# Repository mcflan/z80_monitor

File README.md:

# Z80 Monitor

</img>

A device that allows a host PC to read and write memory on the bus of a Z80
computer (or potentially other CPUs) as well as a few other functions. It makes
use of the Z80's BUSRQ / BUSAK feature to gain access to the bus while the CPU
is running. The circuit is based on an Atmel atmega1281. The host interface is
a bidirectional TTL-level serial (UART) connection that uses a simple hex-based
protocol to control the monitor and provide handshaking. The host interface is
electrically isolated to allow the target device to be power-cycled properly
without being back-powered by the serial signals. This also avoids any risk of
SCR latch-up.

## Host Connector

This is 6-way single-row header to fit a standard FTDI FT232 serial cable (TTL type.) It will work with the 5V and 3V3 versions.

 | Number | Function      |
 |:------:|:------------- |
 |  6     | Not Used      |
 |  5     | Serial Out    |
 |  4     | Serial In     |
 |  3     | Power In      |
 |  2     | Not Used      |
 |  1     | Ground        |

## Bus Connector

See the [pinout file](bus_pinout.md)

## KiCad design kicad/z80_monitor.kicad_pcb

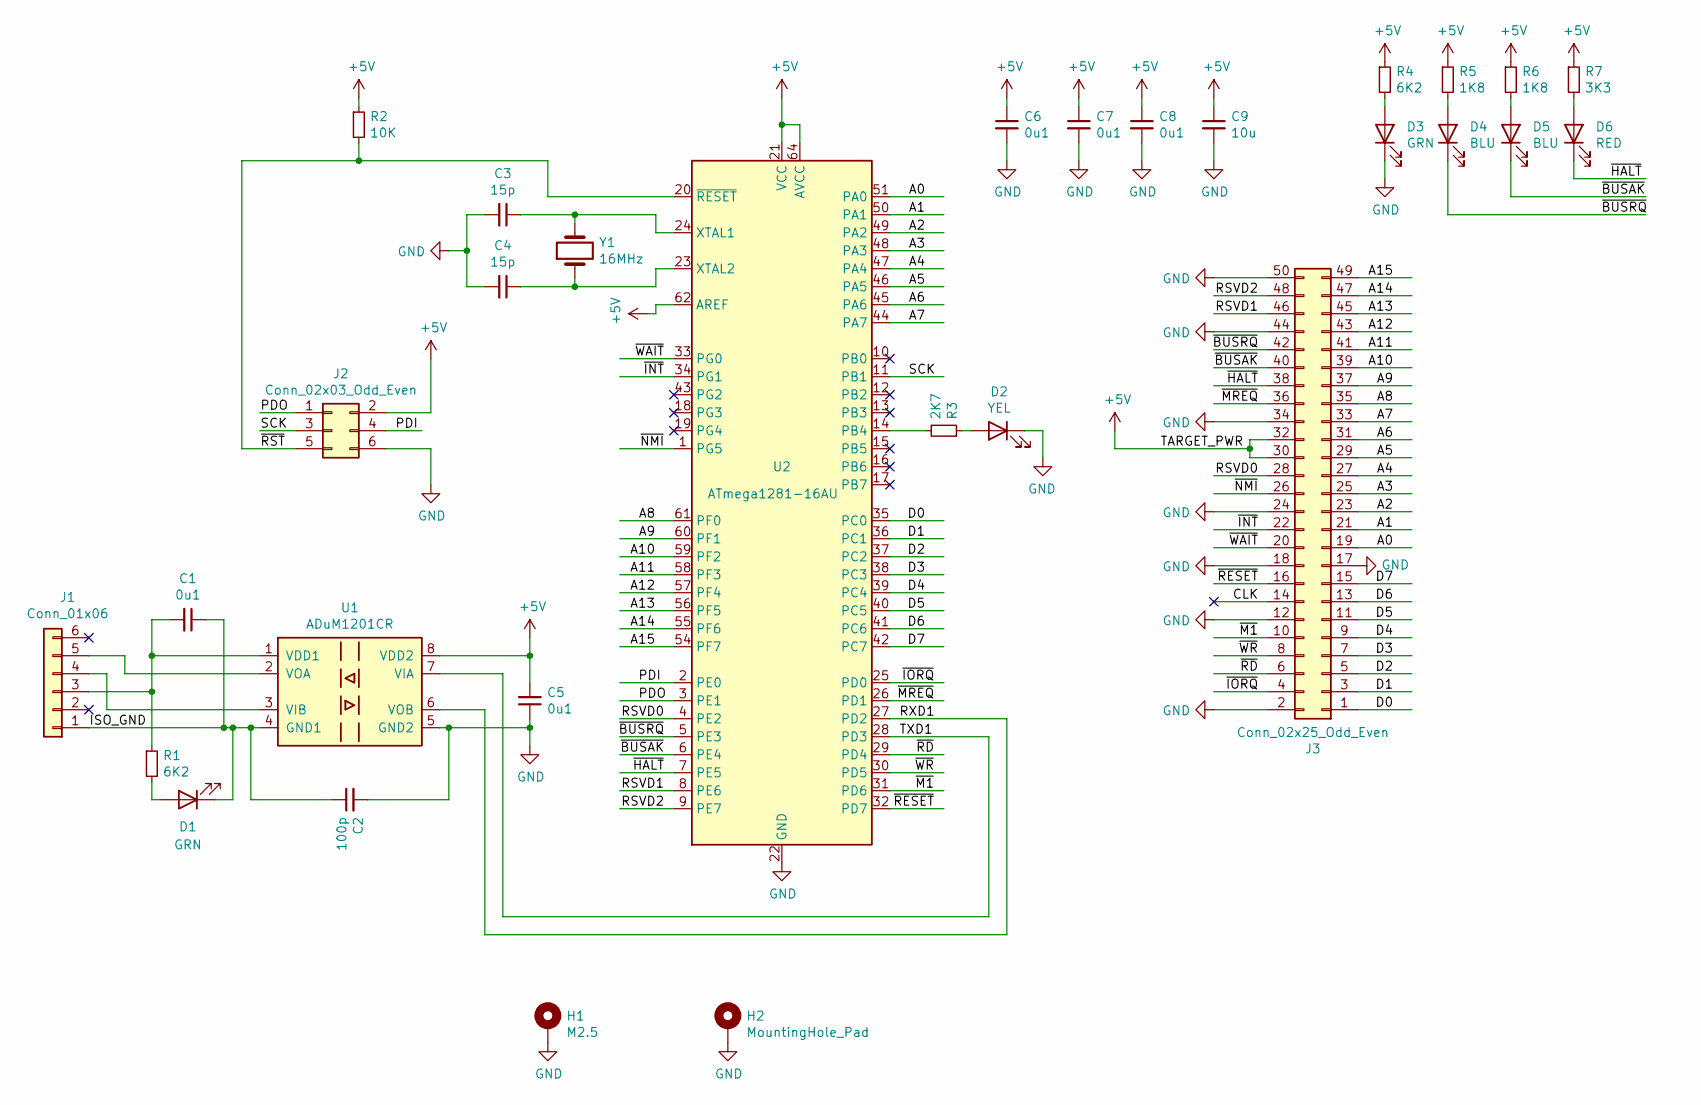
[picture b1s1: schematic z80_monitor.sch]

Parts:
C1, C5, C6, C7, C8: 0u1; C_0603_1608Metric_Pad1.05x0.95mm_HandSolder
C2: 100p; C_0603_1608Metric_Pad1.05x0.95mm_HandSolder
C3, C4: 15p; C_0603_1608Metric_Pad1.05x0.95mm_HandSolder
C9: 10u; C_1206_3216Metric_Pad1.42x1.75mm_HandSolder
D1, D3: GRN; LED_0603_1608Metric_Pad1.05x0.95mm_HandSolder
D2: YEL; LED_0603_1608Metric_Pad1.05x0.95mm_HandSolder
D4, D5: BLU; LED_0603_1608Metric_Pad1.05x0.95mm_HandSolder
D6: RED; LED_0603_1608Metric_Pad1.05x0.95mm_HandSolder
H1: M2.5; MountingHole_2.7mm_M2.5_Pad_Via
H2: MountingHole_Pad; MountingHole_2.7mm_M2.5_Pad_Via
J1: Conn_01x06; PinHeader_1x06_P2.54mm_Vertical
J2: Conn_02x03_Odd_Even; PinHeader_2x03_P2.54mm_Vertical
J3: Conn_02x25_Odd_Even; IDC-Header_2x25_P2.54mm_Vertical
R1, R4: 6K2; R_0603_1608Metric_Pad1.05x0.95mm_HandSolder
R2: 10K; R_0603_1608Metric_Pad1.05x0.95mm_HandSolder
R3: 2K7; R_0603_1608Metric_Pad1.05x0.95mm_HandSolder
R5, R6: 1K8; R_0603_1608Metric_Pad1.05x0.95mm_HandSolder
R7: 3K3; R_0603_1608Metric_Pad1.05x0.95mm_HandSolder
U1: ADuM1201CR; SOIC-8_3.9x4.9mm_P1.27mm
U2: ATmega1281-16AU; TQFP-64_14x14mm_Pitch0.8mm; Farnell 1455092
Y1: 16MHz; Crystal_SMD_Abracon_ABM3-2Pin_5.0x3.2mm_HandSoldering; Farnell 2467791

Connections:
+5V: C5.2, C6.1, C7.1, C8.1, C9.1, J2.2, J3.30, J3.32, R2.1, R4.1, R5.1, R6.1, R7.1, U1.8 (VDD2), U2.21 (VCC), U2.52 (VCC), U2.62 (AREF), U2.64 (AVCC)
/A0: J3.19, U2.51 (PA0)
/A1: J3.21, U2.50 (PA1)
/A2: J3.23, U2.49 (PA2)
/A3: J3.25, U2.48 (PA3)
/A4: J3.27, U2.47 (PA4)
/A5: J3.29, U2.46 (PA5)
/A6: J3.31, U2.45 (PA6)
/A7: J3.33, U2.44 (PA7)
/A8: J3.35, U2.61 (PF0)
/A9: J3.37, U2.60 (PF1)
/A10: J3.39, U2.59 (PF2)
/A11: J3.41, U2.58 (PF3)
/A12: J3.43, U2.57 (PF4)
/A13: J3.45, U2.56 (PF5)
/A14: J3.47, U2.55 (PF6)
/A15: J3.49, U2.54 (PF7)
/CLK: J3.14
/D0: J3.1, U2.35 (PC0)
/D1: J3.3, U2.36 (PC1)
/D2: J3.5, U2.37 (PC2)
/D3: J3.7, U2.38 (PC3)
/D4: J3.9, U2.39 (PC4)
/D5: J3.11, U2.40 (PC5)
/D6: J3.13, U2.41 (PC6)
/D7: J3.15, U2.42 (PC7)
/ISO_GND: C1.1, C2.1, D1.1 (K), J1.1, U1.4 (GND1)
/PDI: J2.4, U2.2 (PE0)
/PDO: J2.1, U2.3 (PE1)
/RSVD0: J3.28, U2.4 (PE2)
/RSVD1: J3.46, U2.8 (PE6)
/RSVD2: J3.48, U2.9 (PE7)
/RXD1: U1.6 (VOB), U2.27 (PD2)
/SCK: J2.3, U2.11 (PB1)
/TXD1: U1.7 (VIA), U2.28 (PD3)
/~BUSAK~: D5.1 (K), J3.40, U2.6 (PE4)
/~BUSRQ~: D4.1 (K), J3.42, U2.5 (PE3)
/~HALT~: D6.1 (K), J3.38, U2.7 (PE5)
/~INT~: J3.22, U2.34 (PG1)
/~IORQ~: J3.4, U2.25 (PD0)
/~M1~: J3.10, U2.31 (PD6)
/~MREQ~: J3.36, U2.26 (PD1)
/~NMI~: J3.26, U2.1 (PG5)
/~RD~: J3.6, U2.29 (PD4)
/~RESET~: J3.16, U2.32 (PD7)
/~RST~: J2.5, R2.2, U2.20 (~RESET)
/~WAIT~: J3.20, U2.33 (PG0)
/~WR~: J3.8, U2.30 (PD5)
GND: C2.2, C3.2, C4.2, C5.1, C6.2, C7.2, C8.2, C9.2, D2.1 (K), D3.1 (K), H1.1, H2.1, J2.6, J3.2, J3.12, J3.17, J3.18, J3.24, J3.34, J3.44, J3.50, U1.5 (GND2), U2.22 (GND), U2.53 (GND), U2.63 (GND)
unnamed: C1.2, J1.3, R1.1, U1.1 (VDD1)
unnamed: C3.1, U2.24 (XTAL1), Y1.2
unnamed: C4.1, U2.23 (XTAL2), Y1.1
unnamed: D1.2 (A), R1.2
unnamed: D2.2 (A), R3.1
unnamed: D3.2 (A), R4.2
unnamed: D4.2 (A), R5.2
unnamed: D5.2 (A), R6.2
unnamed: D6.2 (A), R7.2
unnamed: J1.4, U1.3 (VIB)
unnamed: J1.5, U1.2 (VOA)
unnamed: R3.2, U2.14 (PB4)

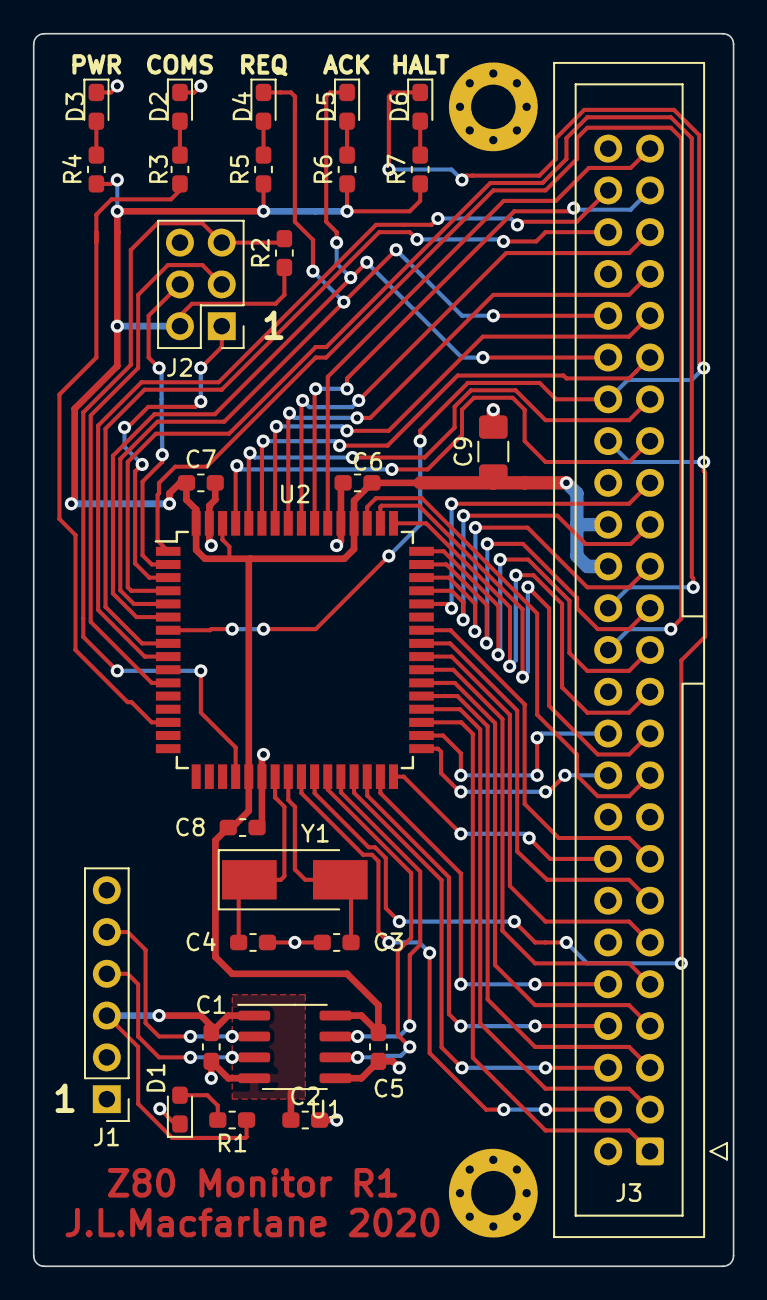
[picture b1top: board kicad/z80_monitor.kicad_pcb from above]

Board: 2 copper layers, 42.5 x 74.9 mm, 30 parts (0 on the bottom side), 60 nets.

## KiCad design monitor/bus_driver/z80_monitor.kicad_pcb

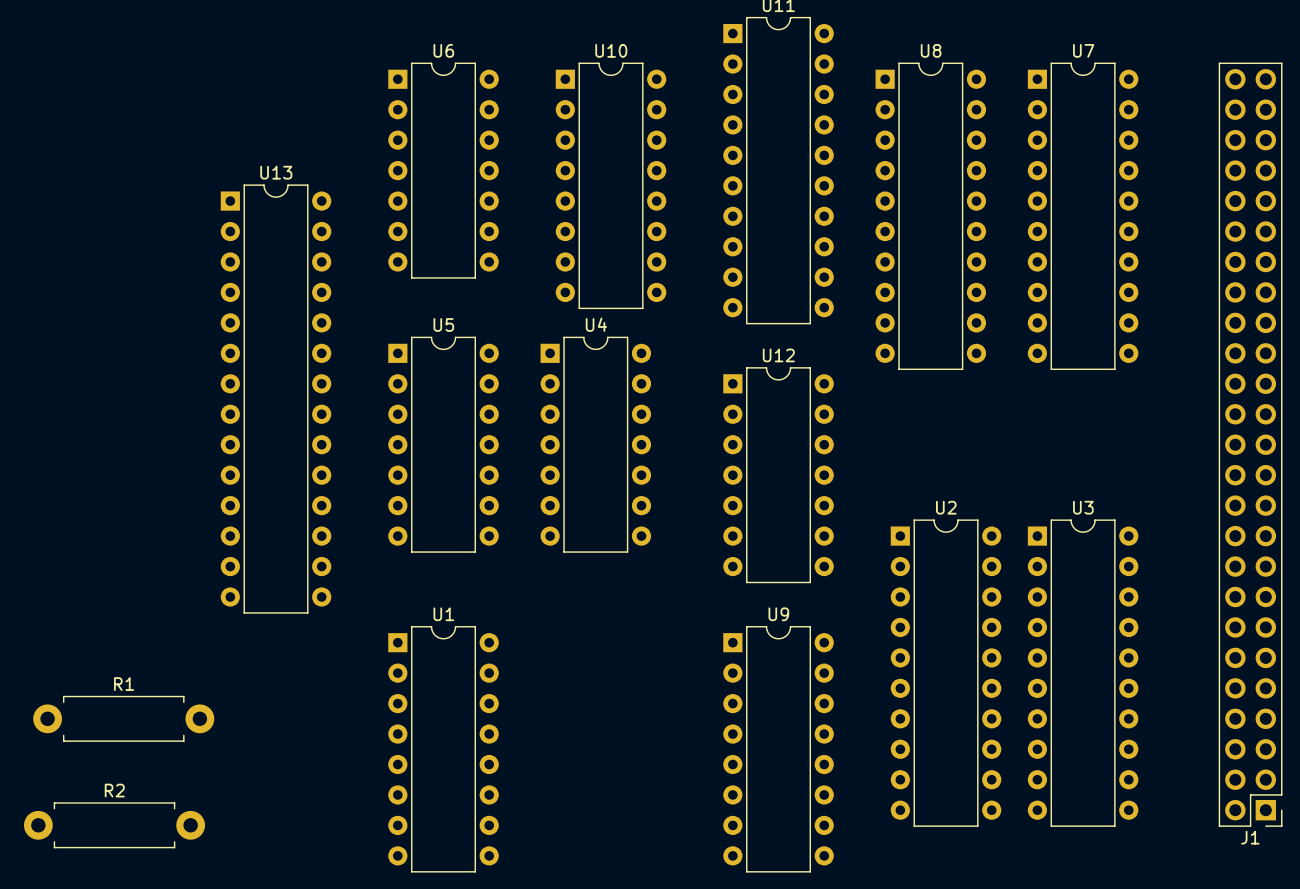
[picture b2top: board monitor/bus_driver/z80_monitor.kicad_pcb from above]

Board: 2 copper layers, 16 parts (0 on the bottom side), 69 nets, no tracks yet.

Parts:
J1: Conn_02x25_Odd_Even; Pin_Header_Straight_2x25_Pitch2.54mm
R1, R2: R_Small; R_Axial_DIN0411_L9.9mm_D3.6mm_P12.70mm_Horizontal
U1: 74HC237; DIP-16_W7.62mm
U2: 74HCT245; DIP-20_W7.62mm
U3, U7, U8, U11: 74HC573; DIP-20_W7.62mm
U4: 74LS04; DIP-14_W7.62mm
U5: 74HC32; DIP-14_W7.62mm
U6: 74LS00; DIP-14_W7.62mm
U9, U10: 74HCT365; DIP-16_W7.62mm
U12: 74LS05; DIP-14_W7.62mm
U13: ATmega328P-PU; DIP-28_W7.62mm

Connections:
+5V: U2.20, U3.20, U7.20, U8.20, U9.16, U10.16, U11.20
/Sheet5FC6B3A2/A0: J1.19, U7.12
/Sheet5FC6B3A2/A1: J1.21, U7.13
/Sheet5FC6B3A2/A2: J1.23, U7.14
/Sheet5FC6B3A2/A3: J1.25, U7.15
/Sheet5FC6B3A2/A4: J1.27, U7.16
/Sheet5FC6B3A2/A5: J1.29, U7.17
/Sheet5FC6B3A2/A6: J1.31, U7.18
/Sheet5FC6B3A2/A7: J1.33, U7.19
/Sheet5FC6B3A2/A8: J1.35, U8.12
/Sheet5FC6B3A2/A9: J1.37, U8.13
/Sheet5FC6B3A2/A10: J1.39, U8.14
/Sheet5FC6B3A2/A11: J1.41, U8.15
/Sheet5FC6B3A2/A12: J1.43, U8.16
/Sheet5FC6B3A2/A13: J1.45, U8.17
/Sheet5FC6B3A2/A14: J1.47, U8.18
/Sheet5FC6B3A2/A15: J1.49, U8.19
/Sheet5FC6B3A2/CYCLE: U6.2, U6.5, U6.10, U6.13
/Sheet5FC6B3A2/D0: J1.1, U2.11, U3.12
/Sheet5FC6B3A2/D1: J1.3, U2.12, U3.13
/Sheet5FC6B3A2/D2: J1.5, U2.13, U3.14
/Sheet5FC6B3A2/D3: J1.7, U2.14, U3.15
/Sheet5FC6B3A2/D4: J1.9, U2.15, U3.16
/Sheet5FC6B3A2/D5: J1.11, U2.16, U3.17
/Sheet5FC6B3A2/D6: J1.13, U2.17, U3.18
/Sheet5FC6B3A2/D7: J1.15, U2.18, U3.19
/Sheet5FC6B3A2/MREQ_~IORQ~: U4.5, U6.9, U11.15
/Sheet5FC6B3A2/TARGET_PWR: J1.30, J1.32, R1.1, R2.1, U4.9, U10.2
/Sheet5FC6B3A2/XD0: U2.9, U3.9, U7.9, U8.9, U10.13, U11.9
/Sheet5FC6B3A2/XD1: U2.8, U3.8, U7.8, U8.8, U10.11, U11.8
/Sheet5FC6B3A2/XD2: U2.7, U3.7, U7.7, U8.7, U10.9, U11.7
/Sheet5FC6B3A2/XD3: U2.6, U3.6, U7.6, U8.6, U10.7, U11.6
/Sheet5FC6B3A2/XD4: U2.5, U3.5, U7.5, U8.5, U10.5, U11.5
/Sheet5FC6B3A2/XD5: U2.4, U3.4, U7.4, U8.4, U10.3, U11.4
/Sheet5FC6B3A2/XD6: U2.3, U3.3, U7.3, U8.3, U11.3
/Sheet5FC6B3A2/XD7: U2.2, U3.2, U7.2, U8.2, U11.2
/Sheet5FC6B3A2/~BUSAK~: J1.40, R1.2, U5.5, U10.4
/Sheet5FC6B3A2/~BUSRQ~: J1.42, U12.2
/Sheet5FC6B3A2/~BUS_EN~: U5.2, U5.6, U7.1, U8.1, U9.1
/Sheet5FC6B3A2/~IORQ~: J1.4, U9.9
/Sheet5FC6B3A2/~M1_UB~: U9.12, U11.14
/Sheet5FC6B3A2/~M1~: J1.10, U9.11
/Sheet5FC6B3A2/~MREQ~: J1.36, U9.7
/Sheet5FC6B3A2/~NMI~: J1.26, U12.6
/Sheet5FC6B3A2/~RD~: J1.6, U9.5
/Sheet5FC6B3A2/~RESET~: J1.16, U12.4
/Sheet5FC6B3A2/~WR~: J1.8, U9.3
GND: J1.2, J1.12, J1.17, J1.18, J1.24, J1.34, J1.44, J1.50, R2.2, U2.1, U2.10, U3.10, U7.10, U8.10, U9.8, U9.15, U10.8, U10.15, U11.1, U11.10
unnamed: U1.5, U1.8
unnamed: U1.10, U4.3
unnamed: U1.11, U4.1, U5.1, U6.4
unnamed: U1.12, U8.11
unnamed: U1.13, U7.11
unnamed: U1.14, U11.11
unnamed: U1.15, U3.11, U6.1
unnamed: U2.19, U4.2
unnamed: U3.1, U5.3
unnamed: U4.6, U6.12
unnamed: U4.8, U5.4
unnamed: U6.3, U9.2
unnamed: U6.6, U9.4
unnamed: U6.8, U9.6
unnamed: U6.11, U9.10
unnamed: U4.4, U10.1
unnamed: U11.16, U12.9
unnamed: U11.17, U12.5
unnamed: U11.18, U12.3
unnamed: U11.19, U12.1
unnamed: U13.8, U13.22

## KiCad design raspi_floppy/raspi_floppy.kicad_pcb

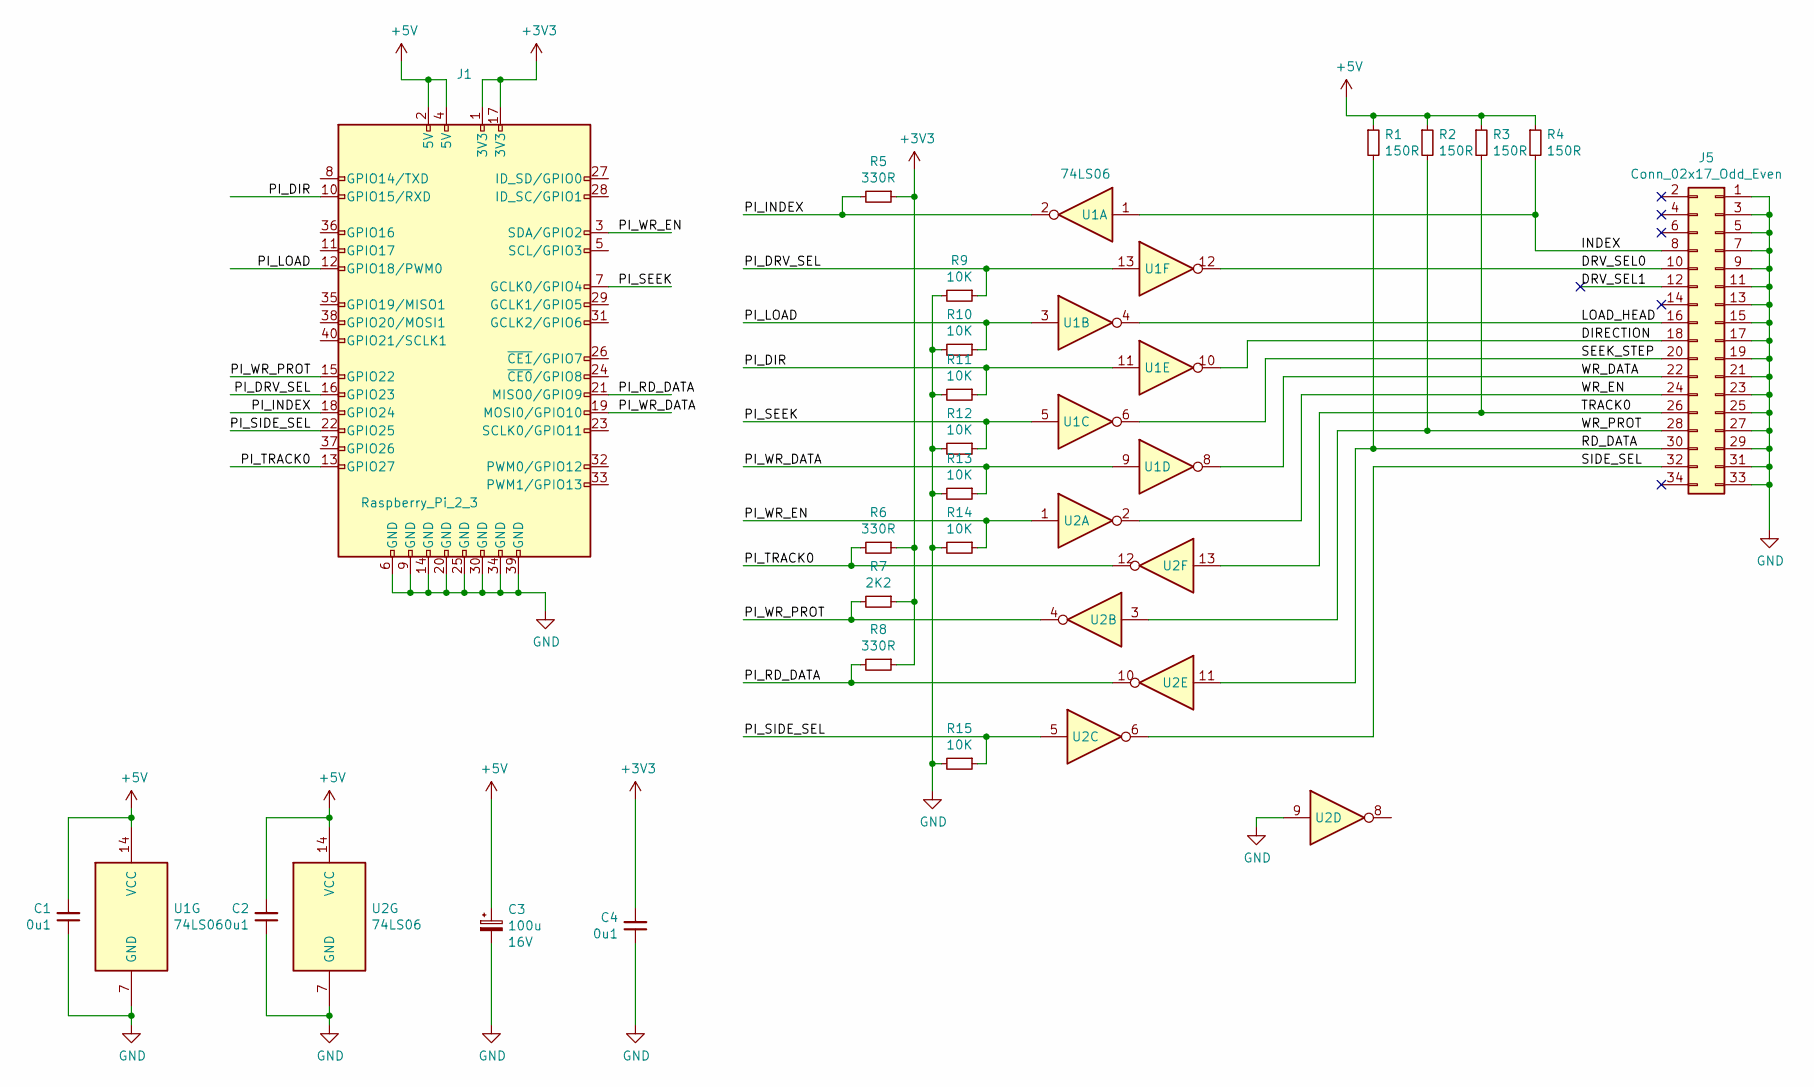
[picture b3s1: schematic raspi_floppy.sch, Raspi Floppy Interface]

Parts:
C1, C2, C4: 0u1; C_Disc_D3.4mm_W2.1mm_P2.50mm
C3: 100u; CP_Radial_D8.0mm_P2.50mm; Voltage 16V
J1: Raspberry_Pi_2_3; HE10-40D
J5: Conn_02x17_Odd_Even; he10-34c
R1, R2: 150R; R_Axial_DIN0207_L6.3mm_D2.5mm_P7.62mm_Horizontal
R3, R4: 150R; R_Axial_DIN0207_L6.3mm_D2.5mm_P2.54mm_Vertical
R5, R6, R8: 330R; R_Axial_DIN0207_L6.3mm_D2.5mm_P10.16mm_Horizontal
R7: 2K2; R_Axial_DIN0207_L6.3mm_D2.5mm_P10.16mm_Horizontal
R9, R10, R11, R12, R13, R14, R15: 10K; R_Axial_DIN0207_L6.3mm_D2.5mm_P10.16mm_Horizontal
U1, U2: 74LS06; DIP-14_W7.62mm

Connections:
+3V3: C4.2, J1.1 (3V3), J1.17 (3V3), R5.1, R6.1, R7.1, R8.1
+5V: C1.2, C2.2, C3.1, J1.2 (5V), J1.4 (5V), R1.1, R2.1, R3.1, R4.1, U1.14 (VCC), U2.14 (VCC)
/DIRECTION: J5.18, U1.10
/DRV_SEL0: J5.10, U1.12
/DRV_SEL1: J5.12
/INDEX: J5.8, R4.2, U1.1
/LOAD_HEAD: J5.16, U1.4
/PI_DIR: J1.10 (GPIO15/RXD), R11.1, U1.11
/PI_DRV_SEL: J1.16 (GPIO23), R9.1, U1.13
/PI_INDEX: J1.18 (GPIO24), R5.2, U1.2
/PI_LOAD: J1.12 (GPIO18/PWM0), R10.1, U1.3
/PI_RD_DATA: J1.21 (MISO0/GPIO9), R8.2, U2.10
/PI_SEEK: J1.7 (GCLK0/GPIO4), R12.1, U1.5
/PI_SIDE_SEL: J1.22 (GPIO25), R15.1, U2.5
/PI_TRACK0: J1.13 (GPIO27), R6.2, U2.12
/PI_WR_DATA: J1.19 (MOSI0/GPIO10), R13.1, U1.9
/PI_WR_EN: J1.3 (SDA/GPIO2), R14.1, U2.1
/PI_WR_PROT: J1.15 (GPIO22), R7.2, U2.4
/RD_DATA: J5.30, R1.2, U2.11
/SEEK_STEP: J5.20, U1.6
/SIDE_SEL: J5.32, U2.6
/TRACK0: J5.26, R3.2, U2.13
/WR_DATA: J5.22, U1.8
/WR_EN: J5.24, U2.2
/WR_PROT: J5.28, R2.2, U2.3
GND: C1.1, C2.1, C3.2, C4.1, J1.6 (GND), J1.9 (GND), J1.14 (GND), J1.20 (GND), J1.25 (GND), J1.30 (GND), J1.34 (GND), J1.39 (GND), J5.1, J5.3, J5.5, J5.7, J5.9, J5.11, J5.13, J5.15, J5.17, J5.19, J5.21, J5.23, J5.25, J5.27, J5.29, J5.31, J5.33, R9.2, R10.2, R11.2, R12.2, R13.2, R14.2, R15.2, U1.7 (GND), U2.7 (GND), U2.9

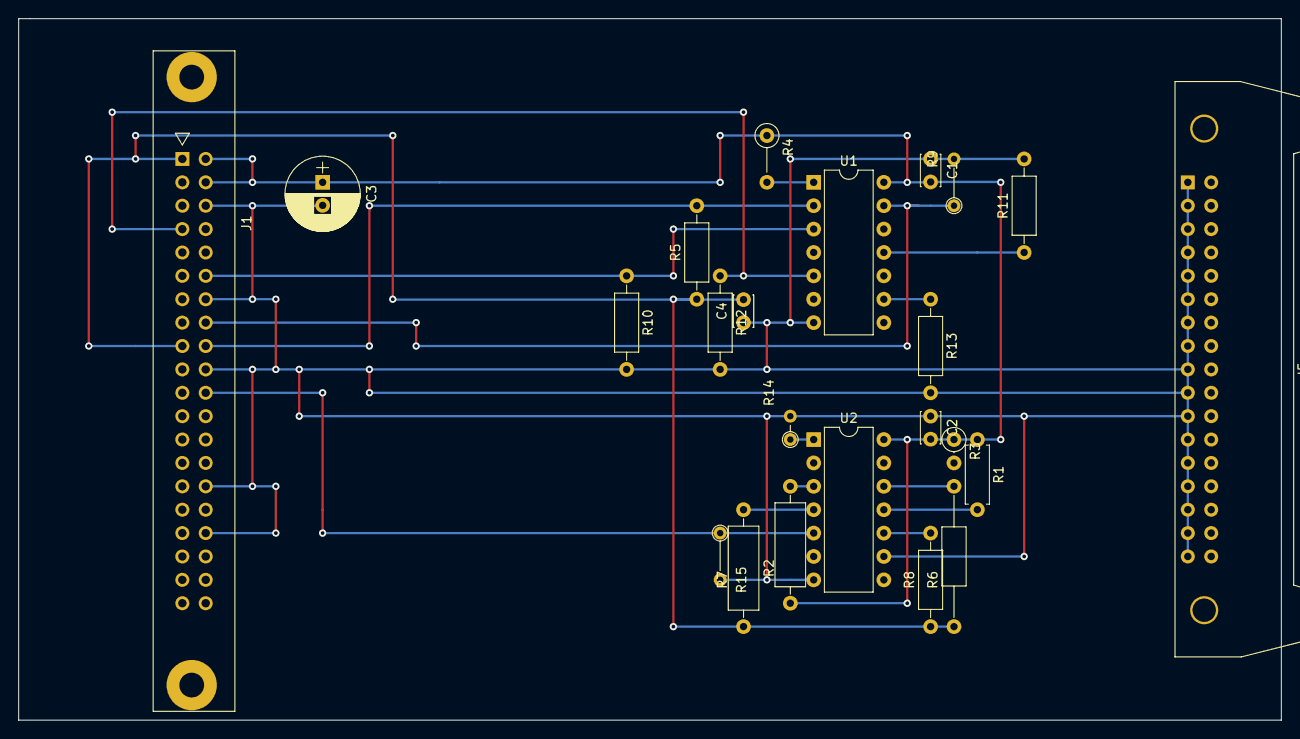
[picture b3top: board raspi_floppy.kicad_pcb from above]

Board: 2 copper layers, 137.2 x 76.2 mm, 23 parts (0 on the bottom side), 25 nets.

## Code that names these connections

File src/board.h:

#ifndef BOARD_H
#define BOARD_H

/* CPU frequency */
#define F_CPU 16000000UL

#include <avr/io.h>

#define COM_CDEV                   (UART1_CDEV)

/* timing */

/* Main timer - 100 Hz */
#define TIMER1_PRESCALE             (8)
#define TIMER1_RATE                 (100)
#define TIMER1_RELOAD               (F_CPU/TIMER1_PRESCALE/TIMER1_RATE)

#define RATE(x) (x * TIMER1_RATE)


/* soft timer designations */
#define ST_UART                     (0)
#define ST_WAIT                     (1)
#define ST_LED                      (2)
#define ST_FIX                      (3)


/* I/O pins */
#define AL_PORT                     (PORTA)
#define AL_DDR                      (DDRA)
#define AH_PORT                     (PORTF)
#define AH_DDR                      (DDRF)

#define DA_PORT                     (PORTC)
#define DA_PIN                      (PINC)
#define DA_DDR                      (DDRC)

#define CTRL_PORT                   (PORTD)
#define CTRL_PIN                    (PIND)
#define CTRL_DDR                    (DDRD)

#define IORQ                        (1 << PD0)
#define MREQ                        (1 << PD1)
#define RXD1                        (1 << PD2)
#define TXD1                        (1 << PD3)
#define RD                          (1 << PD4)
#define WR                          (1 << PD5)
#define M1                          (1 << PD6)
#define RESET                       (1 << PD7)

#define RSVD0                       (1 << PE2)
#define BUSRQ                       (1 << PE3)
#define BUSAK                       (1 << PE4)
#define HALT                        (1 << PE5)
#define RSVD1                       (1 << PE6)
#define RSVD2                       (1 << PE7)

#define WAIT                        (1 << PG0)
#define INT                         (1 << PG1)
#define NMI                         (1 << PG5)

#define LEDS_NUMOF                  (1)
#define LED_PORT                    (PORTB)
#define COMS_LED                    (0)
#define COMS_LED_PIN                (4)


enum {
    MEM_TYPE_MEM = 0,
    MEM_TYPE_IO = 1,
};



/* ADC - Vref is set by an external reference as of PCB Rev.4 */
#define VREF                        (2.500)
#define ADC_BITS                    (10)
/* divide by 64, which gives 125KHz ADC clock for 8MHZ xtal */
#define ADC_CLOCK_DIVIDER (6)

char sleep_read(int fd, int timeout);

#endif /* BOARD_H */

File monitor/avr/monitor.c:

/*
 * Z80 Monitor board driver
 *
 * (C) Copyright James L Macfarlane, Airborne Engineering Ltd 2020.
 */

#include "board.h"

#include <avr/io.h>
#include <avr/interrupt.h>
#include <util/delay.h>
#include <avr/io.h>
#include <avr/sleep.h>
#include <avr/pgmspace.h>
#include <avr/eeprom.h>
#include <avr/sleep.h>
#include <avr/cpufunc.h>

#include <stdlib.h>
#include <string.h>
#include <ctype.h>
#include <stdio.h>
#include <math.h>

#include "uart.h"
#include "timer.h"
#include "debug.h"
#include "hexify.h"
#include "poll.h"
#include "monitor.h"

hexify_encoder_t henc;
hexify_decoder_t hdec;

#if defined(GIT_VERSION) && defined(GIT_DATE)
/* Version message */
    #define VERSION_MSG  "# Firmware git hash " GIT_VERSION " " GIT_DATE " Build " __DATE__ " " __TIME__ "\n\n\r"
#else
    #error "GIT_VERSION and/or GIT_DATE not defined."
#endif

#ifdef DEBUG
    uint8_t debug_lvl = 1;
#endif


/*
 * Sleep a number of seconds using interrupt-driven timer.
 */
void wait(float t)
{
    timer_start(ST_WAIT, TIMER_MODE_ONESHOT, RATE(t));
    timer_sleep(ST_WAIT);
}

hexify_decoder_t decoder;


static inline void set_reg_addr(uint8_t x)
{
    PORTC &= ~0x03;
    PORTC |= x & 0x03;
    _NOP(); _NOP(); _NOP(); _NOP();
}

static inline void write(uint8_t x)
{
    DDRD = 0xfc;
    DDRB = 0x03;
    PORTD = x;
    PORTB = x & 3;
    PORTC &= ~NX_WR; // Assert write line
    _NOP(); _NOP(); _NOP(); _NOP(); _NOP(); _NOP();
    PORTC |= NX_WR; // De-assert write line
    _NOP(); _NOP(); _NOP(); _NOP(); _NOP(); _NOP();
}

static inline void write_reg(uint8_t reg_addr, uint8_t x)
{
    set_reg_addr(reg_addr);
    write(x);
}

static inline void write_control(uint8_t x)
{
    write_reg(REG_CONTROL, x);
}

static inline void write_address(uint16_t x)
{
    write_reg(REG_ADDR_L, x & 0xff);
    write_reg(REG_ADDR_H, x >> 8);
}

static inline void write_data(uint8_t x)
{
    write_reg(REG_DATA, x);
}

static inline uint8_t read_data(void)
{
    // Set port direction to input
    DDRD = 0;
    DDRB = 0;
    PORTC &= ~NX_RD; // Assert read line
    _NOP(); _NOP(); _NOP(); _NOP(); _NOP(); _NOP();
    uint8_t x = (PIND & 0xfc) | (PINB & 0x03);
    PORTC |= NX_RD; // De-assert read line
    _NOP(); _NOP(); _NOP(); _NOP(); _NOP(); _NOP();
    return x;
}

static inline void claim_bus(void)
{

    PORTC &= ~NX_BUSRQ; // Assert bus request line
}


static inline void release_bus(void)
{
    PORTC |= NX_BUSRQ; // De-assert bus request line
}


static inline void write_block(uint16_t addr, uint8_t *data, int size)
{
    int i;
    for (i = 0; i < size; i++) {
        write_address(addr++);
        write_data(data[i]);
    }
}

static inline void read_block(uint16_t addr, uint8_t *data, int size)
{
    int i;
    for (i = 0; i < size; i++) {
        write_address(addr++);
        data[i] = read_data();
    }
}

typedef struct mon_s {
    uint16_t addr;
    uint8_t bus_claimed;
    uint8_t view_on;
    uint8_t inc_addr;
    uint8_t mem_type;
    int cmd;
    int count;
    int buf_ptr;
} mon_t;

void update_hardware(mon_t *mon)
{
    if (mon->bus_claimed) {
        claim_bus();
    } else {
        release_bus();
    }
    if (mon->mem_type == 0) write_control(~CTRL_MREQ);
    if (mon->mem_type == 1) write_control(~CTRL_IORQ);

}

static void set_memtype(uint8_t memtype)
{
    if (memtype == 0) write_control(~CTRL_MREQ);
    if (memtype == 1) write_control(~CTRL_IORQ);
}

void mon_init(mon_t *mon)
{
    mon->inc_addr = 0;
    mon->bus_claimed = 0;
    mon->mem_type = 0; // Default to main memory
    mon->buf_ptr = 0;
}

#define RD_BUF_SIZE     (32)
static uint8_t rd_buf[RD_BUF_SIZE];

void do_msg(mon_t *mon, uint8_t type, int len, uint8_t *data)
{
    switch (type) {
        case MSG_WR: {
            // type(1), memtype(1), address(2), data(N), checksum(1)
            int size = len - 3;
            if (size < 0) {
                printf("# Not enough bytes (%d) for message type %d\n", len, type);
                break;
            }
            uint8_t memtype = data[0];
            set_memtype(memtype);
            uint16_t addr = data[1] | (data[2] << 8);
            printf("# Writing %2d bytes at 0x%04X - ", size, addr);
            write_block(addr, data+3, size);
            read_block(addr, rd_buf, size);
            int i;
            for (i = 0; i < size; i++) {
                if ((data+3)[i] != rd_buf[i]) break;
            }
            if (i < size) {
                printf("Error at 0x%04X\n", addr+i);
            } else {
                printf("ok\n");
            }
            break;
        }
        case MSG_RD: {
            uint8_t memtype = data[0];
            set_memtype(memtype);
            uint16_t addr = data[1] | (data[2] << 8);
            int size = data[3];
            if (size > (RD_BUF_SIZE-2)) {
                printf("# Can't read more than %d bytes at a time\n", RD_BUF_SIZE-2);
                break;
            }
            rd_buf[0] = addr & 0xff;
            rd_buf[1] = addr >> 8;
            read_block(addr, rd_buf+2, size);
            hexify_sender_start(&henc, MSG_RD, rd_buf, size+2);
            char c;
            while  (hexify_sender_next(&henc, &c)) cdev_put(EXT_CDEV, c);
            break;
        }
        case MSG_BUS_REQ:
            printf("# Acquire bus\n");
            claim_bus();
            break;
        case MSG_BUS_REL:
            printf("# Release bus\n");
            release_bus();
            break;
        default:
            printf("# Don't know about msg type %2d\n", type);
    }
}

#define MSG_BUF_SIZE     (64)
static uint8_t msgbuf[MSG_BUF_SIZE];

static void main_loop(mon_t *mon)
{
    mon_init(mon);
    update_hardware(mon);
    hexify_recvr_init(&hdec, msgbuf, MSG_BUF_SIZE);
    // Wait for a message to arrive then process it
    while (1) {
        uint8_t type;
        int len;
        char c = cdev_get(EXT_CDEV);
        int ret = hexify_recvr_next(&hdec, c, &type, &len);
        if (ret == 0) {
            do_msg(mon, type, len, msgbuf);
        }
        if (ret < 0) {
            printf("# Hex encoding error %d\n", ret);
        }
    }
}

static mon_t mon;

int main(void)
{
    /*
     * XD[7:2] => PD[7..2], tri-state
     * (PD1 an PD0 used for serial I/F)
     * XD[1..0] => PB[1..], tri-state
     * XA[1..0] => PC[1..0], output
     * /X_RD => PC2, output
     * /X_WR => PC3, output
     * /X_BUSRQ => PC4, output
     *
     * Address map:
     * 0: Write data
     * 1: Address latch A[7..0]
     * 2: Address latch A[15..8]
     * 3: Control register:
     *      Bit 0: !EPROM_EN
     *      Bit 1: !PGM_EN
     *      Bit 2: !MREQ
     *      Bit 3: !IOREQ
     */

    DDRD = 0xff; // Start as all inputs
    DDRB = 0x03;
    DDRC = 0x1f;
    // Start with control outputs de-asserted (high)
    PORTC |= NX_BUSRQ | NX_WR | NX_RD;

    timer_init(TIMER1_RELOAD);

    /* turn on global interrupts */
    sei();

    uart0_init(EXT_CDEV, 8); /* 115200 baud */
    stdout = &uart0_fp;

    cdev_put(EXT_CDEV, '\n');
    cdev_put(EXT_CDEV, '\r');
    PRINT("MCU Monitor. J.Macfarlane 2020\n\r");
    PRINT(VERSION_MSG);

    //hexify_recvr_init(&decoder, (uint8_t *)&rx_msg, XBEE_MSG_LEN);

    release_bus();

    main_loop(&mon);

    return 0;
}

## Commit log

2020-10-27 Add bus layout.
2020-10-27 More updates.
2020-10-28 More pinout updates.
2020-10-28 Update pinouts.
2020-10-28 Add kicad schematic - still work-in-progress.
2020-10-29 UART section of IO board completed.
2020-10-29 Add ignore files and jm_z80 library.
2020-10-29 Add sym lib table.
2020-10-29 Lots more work on schematic
2020-10-29 Name sheets.
2020-10-29 Un-fsck something which made most of the chips into 74LS00 for some very odd reason. Also start to assign footprints.
2020-10-29 Add chache.lib file to git.
2020-10-30 Re-annotateand fix doubled-up U6 unit.
2020-10-30 Add some no-connection symbols.
2020-10-30 Add dcm file for jm_z80 lib.
2020-10-30 Add missing connection for /wait.
2020-10-30 Add some missing gates and wiring.
2020-10-30 Complete RAM_WR_EN wiring.
2020-10-30 Add pull-up for /IORQ on IO board.
2020-10-30 Add eagle files for old z80 monitor board and for mods to make it compatible with new 50 way pinout.
2020-10-30 Add adapter board for old monitor eurocard connector to new 50 way pinout.
2020-10-31 Add description of new bus pinout specs.
2020-10-31 Trying to get overbar on signal names in markdown.
2020-10-31 More updates to pinout.
2020-10-31 Update monitor mods.
2020-10-31 Update to adapter.
2020-11-05 Add a label to eagle schematics.
2020-11-05 Add beginings of arduino monitor code.
2020-11-10 Just echo characters back for now.
2020-11-10 Starting to implement monitor commands.
2020-11-11 Now imports ihex records.
2020-11-11 Add z80 src examples, etc.
2020-11-11 claim bus before writing a block.
2020-11-11 Update Makefile header.
2020-11-11 Move ihex char parsing into own fn.
2020-11-12 Minor updates.
2020-11-14 Add kicad schematic and rough veroboard layout for raspi floppy interface.
2020-11-14 Add cache lib.
2020-11-16 Add missing resnet for keyboard pull-ups.
2020-11-18 Add freeCAD drawing of spacer.
2020-11-18 Update Pi floppy i/f.
2020-11-18 Minor update to schematic.
2020-11-18 Move mkII schematic dir.
2020-11-18 Add g-code for spacer top machining.
2020-11-18 Fix g2/g3 mix-up and missing o101 call.
2020-11-18 Move src dir.
2020-11-18 Add original Z80 binaries.
2020-11-18 Update README's.
2020-11-18 Fix table in md file.
2020-11-18 Rename a dir.
2020-11-19 Add script for disassembling original Z80 binaries.
2020-11-19 Add chamfer.
2020-11-19 Add tool heights. Fix missing brace.
2020-11-19 Move home pos further out, fix some commented-out g42's
2020-11-19 Fix wrong x dim on foot outline.
2020-11-19 Change move-off cmds.
2020-11-19 Fix #9 - should be radius not dia.
2020-11-20 New approach to roughing.
2020-11-20 Seems that f30 at end of a line affects all following lines.
2020-11-20 Move file.
2020-11-20 Split g-code into a file per tool because linuxCNC won't allow manual touch-off when paused.
2020-11-20 Lots of updates to gcode.
2020-11-20 Typo.
2020-11-21 Increase amount to remove in finishing cut to try to re-cut the chips less.
2020-11-21 Increase feed rate.
2020-11-22 Abstract the feed rate and increase by 50%.
2020-11-22 Fix library path for adapter after moving mkII schematic dir.
2020-11-22 Add note to CPU schematic.
2020-11-23 Add some notes about increasing number of hardware upgrades and fixes to mkII.
2020-11-28 Add some code stubs. serial.asm works, display.asm does not, probably due to hardware issues.
2020-11-28 Update keyb3 disassembly.
2020-11-29 Move monitor AVR to own dir.
2020-11-30 Change of plan: get rid of interactive terminal and instead us code on host. This solves problem of flow-control. Add header for magic numbers shared with host monitor code.
2020-11-30 Add monitor host python code. Can write to mem.
2020-11-30 Minor fixes.
2020-11-30 Edit serial.asm
2020-11-30 Can now read data back from monitor.
2020-11-30 Fix pretty-printing.
2020-11-30 Fix cmd line help.
2020-11-30 Some minor tidying-up of monitor code.
2020-12-01 LCD now working
2020-12-03 Add kicad project for new monitor board.
2020-12-03 Assign some footprints and begin to play with layout
2020-12-03 Add some comments.
2020-12-03 Add new minimalist atmega1281-bases monitor.
2020-12-03 Add gitignore.
2020-12-06 Finished new AVR-based monitor board, pending final checks and gerber generation.
2020-12-06 Move LEDs to edge of board and label. Add 2x M2.5 clearance hole.
2020-12-07 Various updates to board.
2020-12-07 More re-arrangement of files.
2020-12-07 Add README.
2020-12-07 Add pic.
2020-12-07 Image update.
2020-12-07 Add gerbers
2020-12-07 Add src dir. Empty atm.
2020-12-07 Re-do gerbers with new settings.
2020-12-07 Add zip.
2020-12-07 Update gerbers.
2020-12-07 Add pinout.
2020-12-07 Rename pinput file.
2021-01-03 Update LED resistor values to try to match brightness.
2021-01-03 Initial commit of monitor AVR code.
2021-01-03 230400 baud doesn't rx properly. Changed to 115200.
2021-01-04 Add code to flush serial input buf in python. Add reset and release functionality.
2021-01-04 Add snag list for PCB.
2021-01-05 Minor tidy-up of python.
2021-01-05 Add NMI command.
2021-01-06 Add command to clear areas of memory.
2021-01-08 Update snaglist. Add INT function.
2021-02-15 Update board
